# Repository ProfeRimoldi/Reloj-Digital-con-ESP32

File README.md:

# Reloj Digital de 6 Dígitos con ESP32

Proyecto de reloj digital basado en **ESP32**, diseñado con fines educativos y de desarrollo de hardware. Utiliza multiplexación de cátodo común controlada por transistores NPN y lógica de desplazamiento eficiente mediante un registro **74HCT595**, garantizando una interfaz robusta y de excelente brillo.

---

## 🚀 Características Principales

* **Controlador Central:** ESP32 (operando con lógica de control a 3.3V).
* **Interfaz de Visualización:** 6 displays de 7 segmentos de **cátodo común** (HH:MM:SS) multiplexados mediante transistores NPN (**BC547**).
* **Registro de Desplazamiento:** Integrado **74HCT595** (variante TTL-compatible), ideal para recibir señales de control a 3.3V del ESP32 mientras alimenta los displays y segmentos a **5V** para asegurar máxima luminosidad.
* **Módulo de Entradas (Pulsadores):** 
  * Botones físicos con red de filtrado **RC** antirrebote.
  * Inversores **Schmitt Trigger (`74HC14`)** alimentados a 3.3V para proteger los pines del microcontrolador y entregar flancos limpios.
* **Separadores:** LEDs separadores (`:`) controlados de forma independiente por transistor NPN para efectos de parpadeo (modo de configuración).

---

## 📌 Tabla de Conexiones Definitiva (ESP32)

| Bloque / Etapa | Señal / Función | Pin ESP32 | Descripción de la Conexión |
| :--- | :--- | :--- | :--- |
| **Entradas (Pulsadores)** | `MODE` (Configuración) | `GPIO 32` | Salida del inversor Schmitt Trigger (74HC14) del botón de Modo. |
| **Entradas (Pulsadores)** | `INC` (Incrementar) | `GPIO 33` | Salida del inversor Schmitt Trigger del botón de aumento. |
| **Entradas (Pulsadores)** | `DEC` (Decrementar) | `GPIO 25` | Salida del inversor Schmitt Trigger del botón de disminución. |
| **Entradas (Pulsadores)** | `SET` (Confirmar/Guardar) | `GPIO 26` | Salida del inversor Schmitt Trigger del botón de selección. |
| **Display (SPI / Shift)** | `DATA` (MOSI / DS) | `GPIO 23` | Conectado al pin DS (Pin 14) del registro 74HCT595. |
| **Display (SPI / Shift)** | `CLOCK` (SCK / SRCLK)| `GPIO 18` | Conectado al pin SRCLK (Pin 11) del registro 74HCT595. |
| **Display (SPI / Shift)** | `LATCH` (Storage / RCLK)| `GPIO 5` | Conectado al pin RCLK (Pin 12) del registro 74HCT595. |
| **Multiplexado** | `SEL1` (Horas - Decena) | `GPIO 13` | Base del transistor BC547 (Dígito 1) vía resistencia $4.7\text{ k}\Omega$. |
| **Multiplexado** | `SEL2` (Horas - Unidad) | `GPIO 12` | Base del transistor BC547 (Dígito 2) vía resistencia $4.7\text{ k}\Omega$. |
| **Multiplexado** | `SEL3` (Minutos - Decena)| `GPIO 14` | Base del transistor BC547 (Dígito 3) vía resistencia $4.7\text{ k}\Omega$. |
| **Multiplexado** | `SEL4` (Minutos - Unidad)| `GPIO 27` | Base del transistor BC547 (Dígito 4) vía resistencia $4.7\text{ k}\Omega$. |
| **Multiplexado** | `SEL5` (Segundos - Decena)| `GPIO 4` | Base del transistor BC547 (Dígito 5) vía resistencia $4.7\text{ k}\Omega$. |
| **Multiplexado** | `SEL6` (Segundos - Unidad)| `GPIO 15` | Base del transistor BC547 (Dígito 6) vía resistencia $4.7\text{ k}\Omega$. |
| **Interfaz Visual** | `COLON` (LEDs `:` ) | `GPIO 2` | Control de los puntos separadores con resistencia limitadora. |

---

## ⚡ Consideraciones de Diseño y Niveles Lógicos

1. **Alimentación Mixta Segura:** 
   * La etapa de potencia (displays y registro 74HCT595) opera a **5V** para garantizar brillo óptimo.
   * La etapa de control de pulsadores y el inversor Schmitt Trigger (`74HC14`) operan rígidamente a **3.3V** (tomados del regulador interno del ESP32), protegiendo los pines de entrada del microcontrolador.
2. **Compatibilidad HCT:** El uso del `74HCT595` permite recibir comandos a 3.3V desde el ESP32 sin requerir conversores de nivel externos, simplificando drásticamente el circuito impreso.

---

## 🛠️ Autor
**Prof. Damián Rimoldi**

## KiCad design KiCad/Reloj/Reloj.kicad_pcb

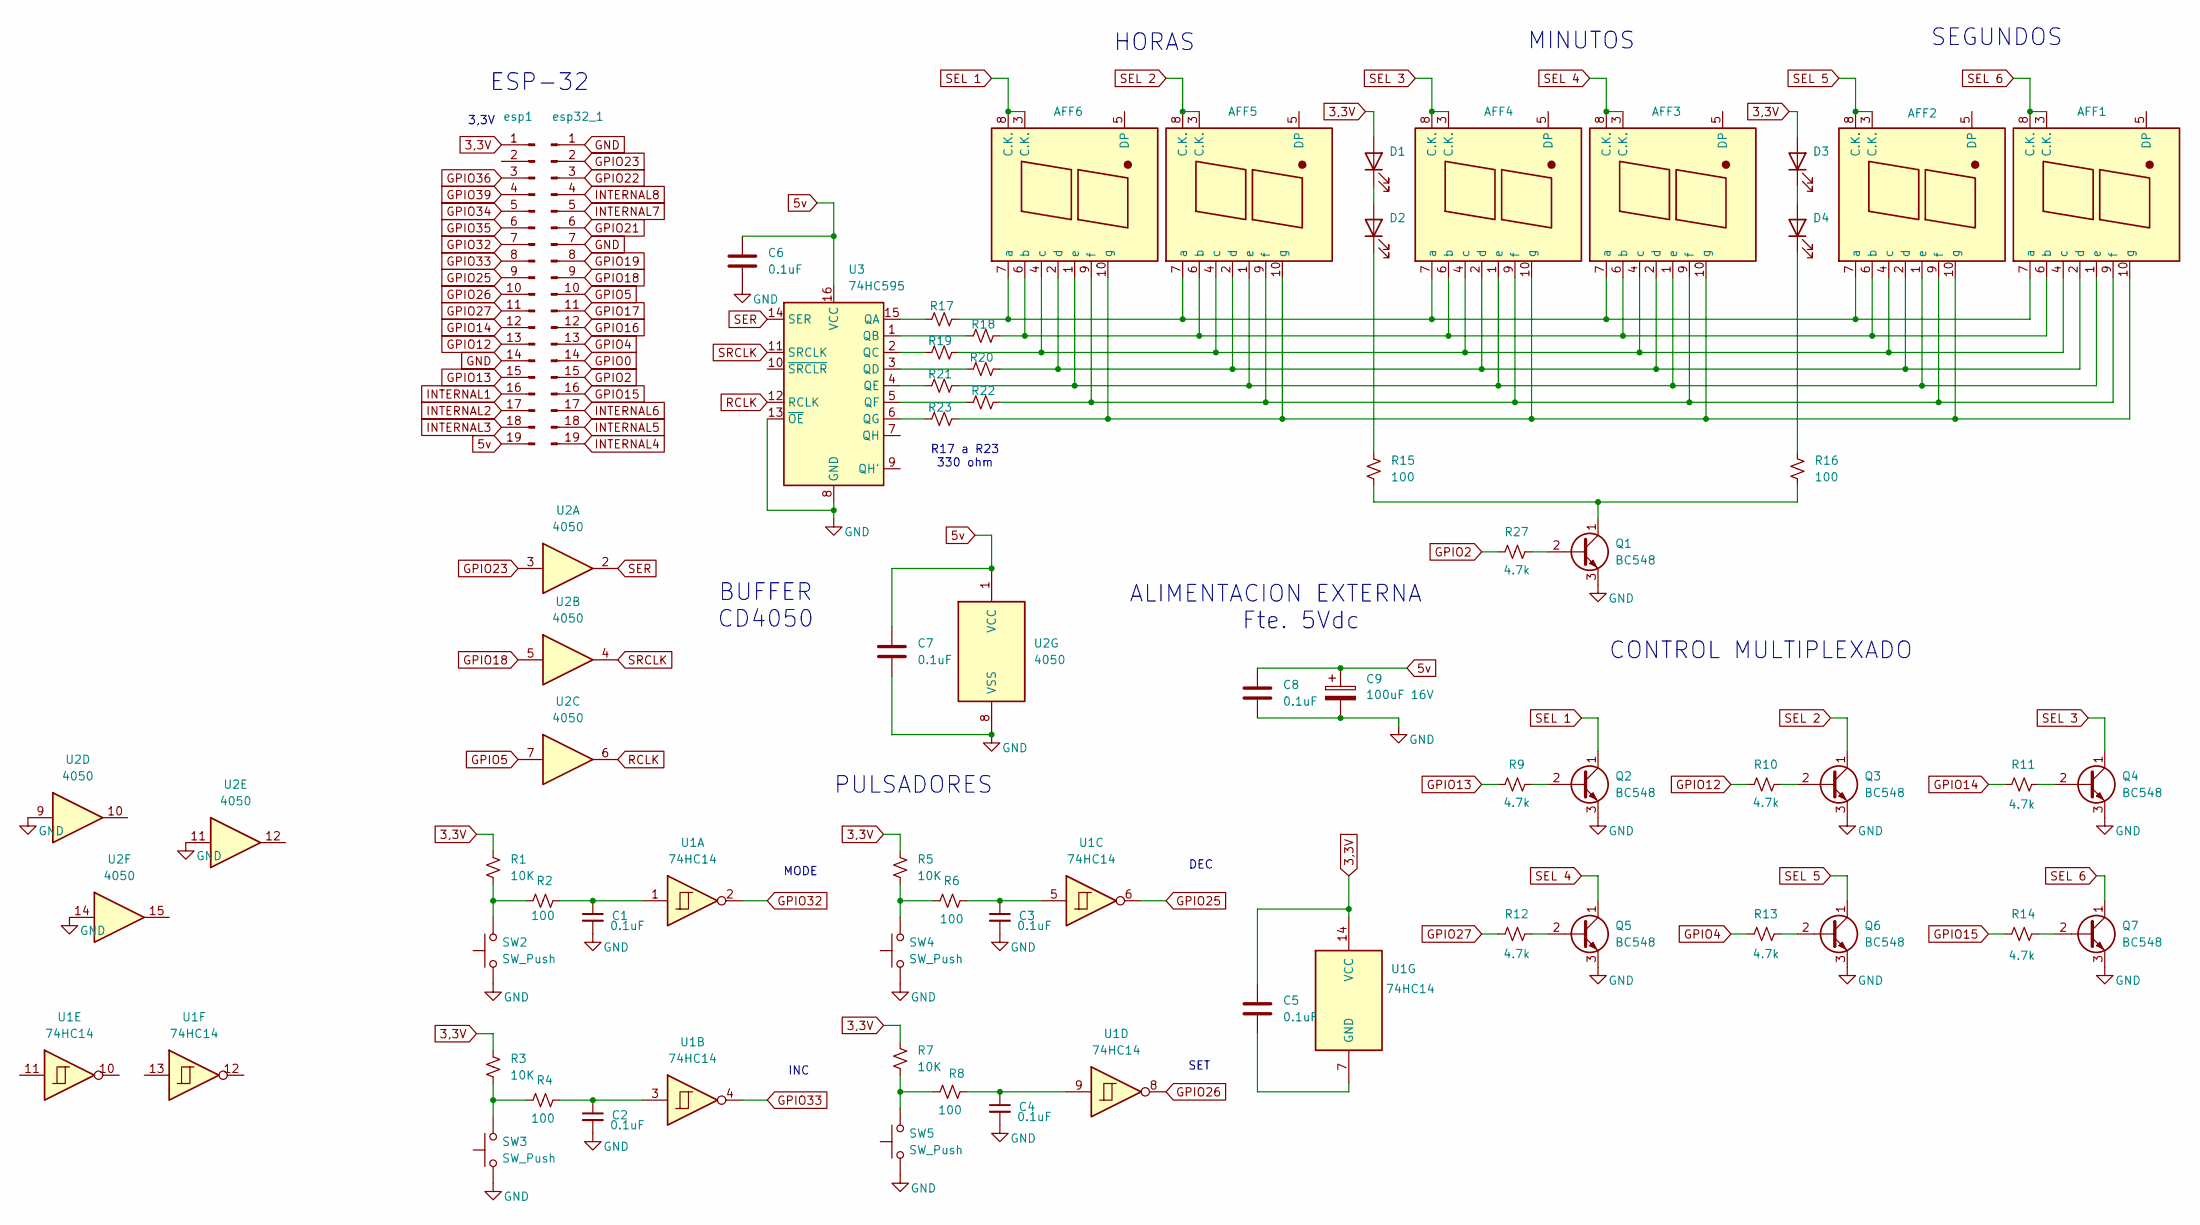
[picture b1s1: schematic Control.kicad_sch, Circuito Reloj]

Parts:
AFF1, AFF2, AFF3, AFF4, AFF5, AFF6: LTS-6980HR; 7SegmentLED_LTS6760_LTS6780
C1, C2, C3, C4, C5, C6, C7, C8: 0.1uF; C_Disc_D5.0mm_W2.5mm_P2.50mm
C9: 100uF 16V; CP_Radial_D6.3mm_P2.50mm
D1, D2, D3, D4: LED; LED_D3.0mm
Q1, Q2, Q3, Q4, Q5, Q6, Q7: BC548; TO-92_Inline
R1, R3, R5, R7: 10K; R_Axial_DIN0204_L3.6mm_D1.6mm_P5.08mm_Horizontal
R2, R4, R6, R8, R15, R16: 100; R_Axial_DIN0204_L3.6mm_D1.6mm_P5.08mm_Horizontal
R9, R10, R11, R12, R13, R14, R27: 4.7k; R_Axial_DIN0204_L3.6mm_D1.6mm_P5.08mm_Horizontal
R17, R18, R19, R20, R21, R22, R23: 330; R_Axial_DIN0204_L3.6mm_D1.6mm_P5.08mm_Horizontal
SW2, SW3, SW4, SW5: SW_Push; SW_PUSH_6mm_H4.3mm
U1: 74HC14; DIP-14_W7.62mm_Socket_LongPads
U2: 4050; DIP-16_W7.62mm_Socket_LongPads
U3: 74HC595; DIP-16_W7.62mm_Socket_LongPads
esp1, esp32_1: Conn_01x19_Pin; PinSocket_1x19_P2.54mm_Vertical

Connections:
3,3V: C5.1, D1.2 (A), D3.2 (A), R1.1, R3.1, R5.1, R7.1, U1.14 (VCC), esp1.1
5v: C6.1, C7.1, C8.1, C9.1, U2.1 (VCC), U3.16 (VCC), esp1.19
GND: C1.2, C2.2, C3.2, C4.2, C6.2, C7.2, C8.2, C9.2, Q1.3 (E), Q2.3 (E), Q3.3 (E), Q4.3 (E), Q5.3 (E), Q6.3 (E), Q7.3 (E), SW2.1, SW3.1, SW4.1, SW5.1, U2.8 (VSS), U2.9, U2.11, U2.14, U3.8 (GND), U3.13 (~OE), esp1.14, esp32_1.1, esp32_1.7
GPIO0: esp32_1.14
GPIO2: R27.2, esp32_1.15
GPIO4: R13.2, esp32_1.13
GPIO5: U2.7, esp32_1.10
GPIO12: R10.2, esp1.13
GPIO13: R9.2, esp1.15
GPIO14: R11.2, esp1.12
GPIO15: R14.2, esp32_1.16
GPIO16: esp32_1.12
GPIO17: esp32_1.11
GPIO18: U2.5, esp32_1.9
GPIO19: esp32_1.8
GPIO21: esp32_1.6
GPIO22: esp32_1.3
GPIO23: U2.3, esp32_1.2
GPIO25: U1.6, esp1.9
GPIO26: U1.8, esp1.10
GPIO27: R12.2, esp1.11
GPIO32: U1.2, esp1.7
GPIO33: U1.4, esp1.8
GPIO34: esp1.5
GPIO35: esp1.6
GPIO36: esp1.3
GPIO39: esp1.4
INTERNAL1: esp1.16
INTERNAL2: esp1.17
INTERNAL3: esp1.18
INTERNAL4: esp32_1.19
INTERNAL5: esp32_1.18
INTERNAL6: esp32_1.17
INTERNAL7: esp32_1.5
INTERNAL8: esp32_1.4
unnamed: AFF1.7 (a), AFF2.7 (a), AFF3.7 (a), AFF4.7 (a), AFF5.7 (a), AFF6.7 (a), R17.1
unnamed: AFF1.6 (b), AFF2.6 (b), AFF3.6 (b), AFF4.6 (b), AFF5.6 (b), AFF6.6 (b), R18.1
unnamed: AFF1.4 (c), AFF2.4 (c), AFF3.4 (c), AFF4.4 (c), AFF5.4 (c), AFF6.4 (c), R19.1
unnamed: AFF1.2 (d), AFF2.2 (d), AFF3.2 (d), AFF4.2 (d), AFF5.2 (d), AFF6.2 (d), R20.1
unnamed: AFF1.1 (e), AFF2.1 (e), AFF3.1 (e), AFF4.1 (e), AFF5.1 (e), AFF6.1 (e), R21.1
unnamed: AFF1.9 (f), AFF2.9 (f), AFF3.9 (f), AFF4.9 (f), AFF5.9 (f), AFF6.9 (f), R22.1
unnamed: AFF1.10 (g), AFF2.10 (g), AFF3.10 (g), AFF4.10 (g), AFF5.10 (g), AFF6.10 (g), R23.1
unnamed: C1.1, R2.1, U1.1
unnamed: C2.1, R4.1, U1.3
unnamed: C3.1, R6.1, U1.5
unnamed: C4.1, R8.1, U1.9
unnamed: D1.1 (K), D2.2 (A)
unnamed: D2.1 (K), R15.1
unnamed: D3.1 (K), D4.2 (A)
unnamed: D4.1 (K), R16.1
unnamed: Q1.2 (B), R27.1
unnamed: Q1.1 (C), R15.2, R16.2
unnamed: Q2.2 (B), R9.1
unnamed: Q3.2 (B), R10.1
unnamed: Q4.2 (B), R11.1
unnamed: Q5.2 (B), R12.1
unnamed: Q6.2 (B), R13.1
unnamed: Q7.2 (B), R14.1
unnamed: R1.2, R2.2, SW2.2
unnamed: R3.2, R4.2, SW3.2
unnamed: R5.2, R6.2, SW4.2
unnamed: R7.2, R8.2, SW5.2
unnamed: C5.2, U1.7 (GND)
unnamed: R17.2, U3.15 (QA)
unnamed: R18.2, U3.1 (QB)
unnamed: R19.2, U3.2 (QC)
unnamed: R20.2, U3.3 (QD)
unnamed: R21.2, U3.4 (QE)
unnamed: R22.2, U3.5 (QF)
unnamed: R23.2, U3.6 (QG)
RCLK: U2.6, U3.12 (RCLK)
SEL 1: AFF6.3 (C.K.), AFF6.8 (C.K.), Q2.1 (C)
SEL 2: AFF5.3 (C.K.), AFF5.8 (C.K.), Q3.1 (C)
SEL 3: AFF4.3 (C.K.), AFF4.8 (C.K.), Q4.1 (C)
SEL 4: AFF3.3 (C.K.), AFF3.8 (C.K.), Q5.1 (C)
SEL 5: AFF2.3 (C.K.), AFF2.8 (C.K.), Q6.1 (C)
SEL 6: AFF1.3 (C.K.), AFF1.8 (C.K.), Q7.1 (C)
SER: U2.2, U3.14 (SER)
SRCLK: U2.4, U3.11 (SRCLK)

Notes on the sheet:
HORAS
SET
SEGUNDOS
3,3V
R17 a R23 330 ohm
PULSADORES
DEC
MINUTOS
ALIMENTACION EXTERNA Fte. 5Vdc
CONTROL MULTIPLEXADO
INC
BUFFER CD4050
MODE
ESP-32

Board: 2 copper layers, 59 parts (0 on the bottom side), 61 nets, no tracks yet.
